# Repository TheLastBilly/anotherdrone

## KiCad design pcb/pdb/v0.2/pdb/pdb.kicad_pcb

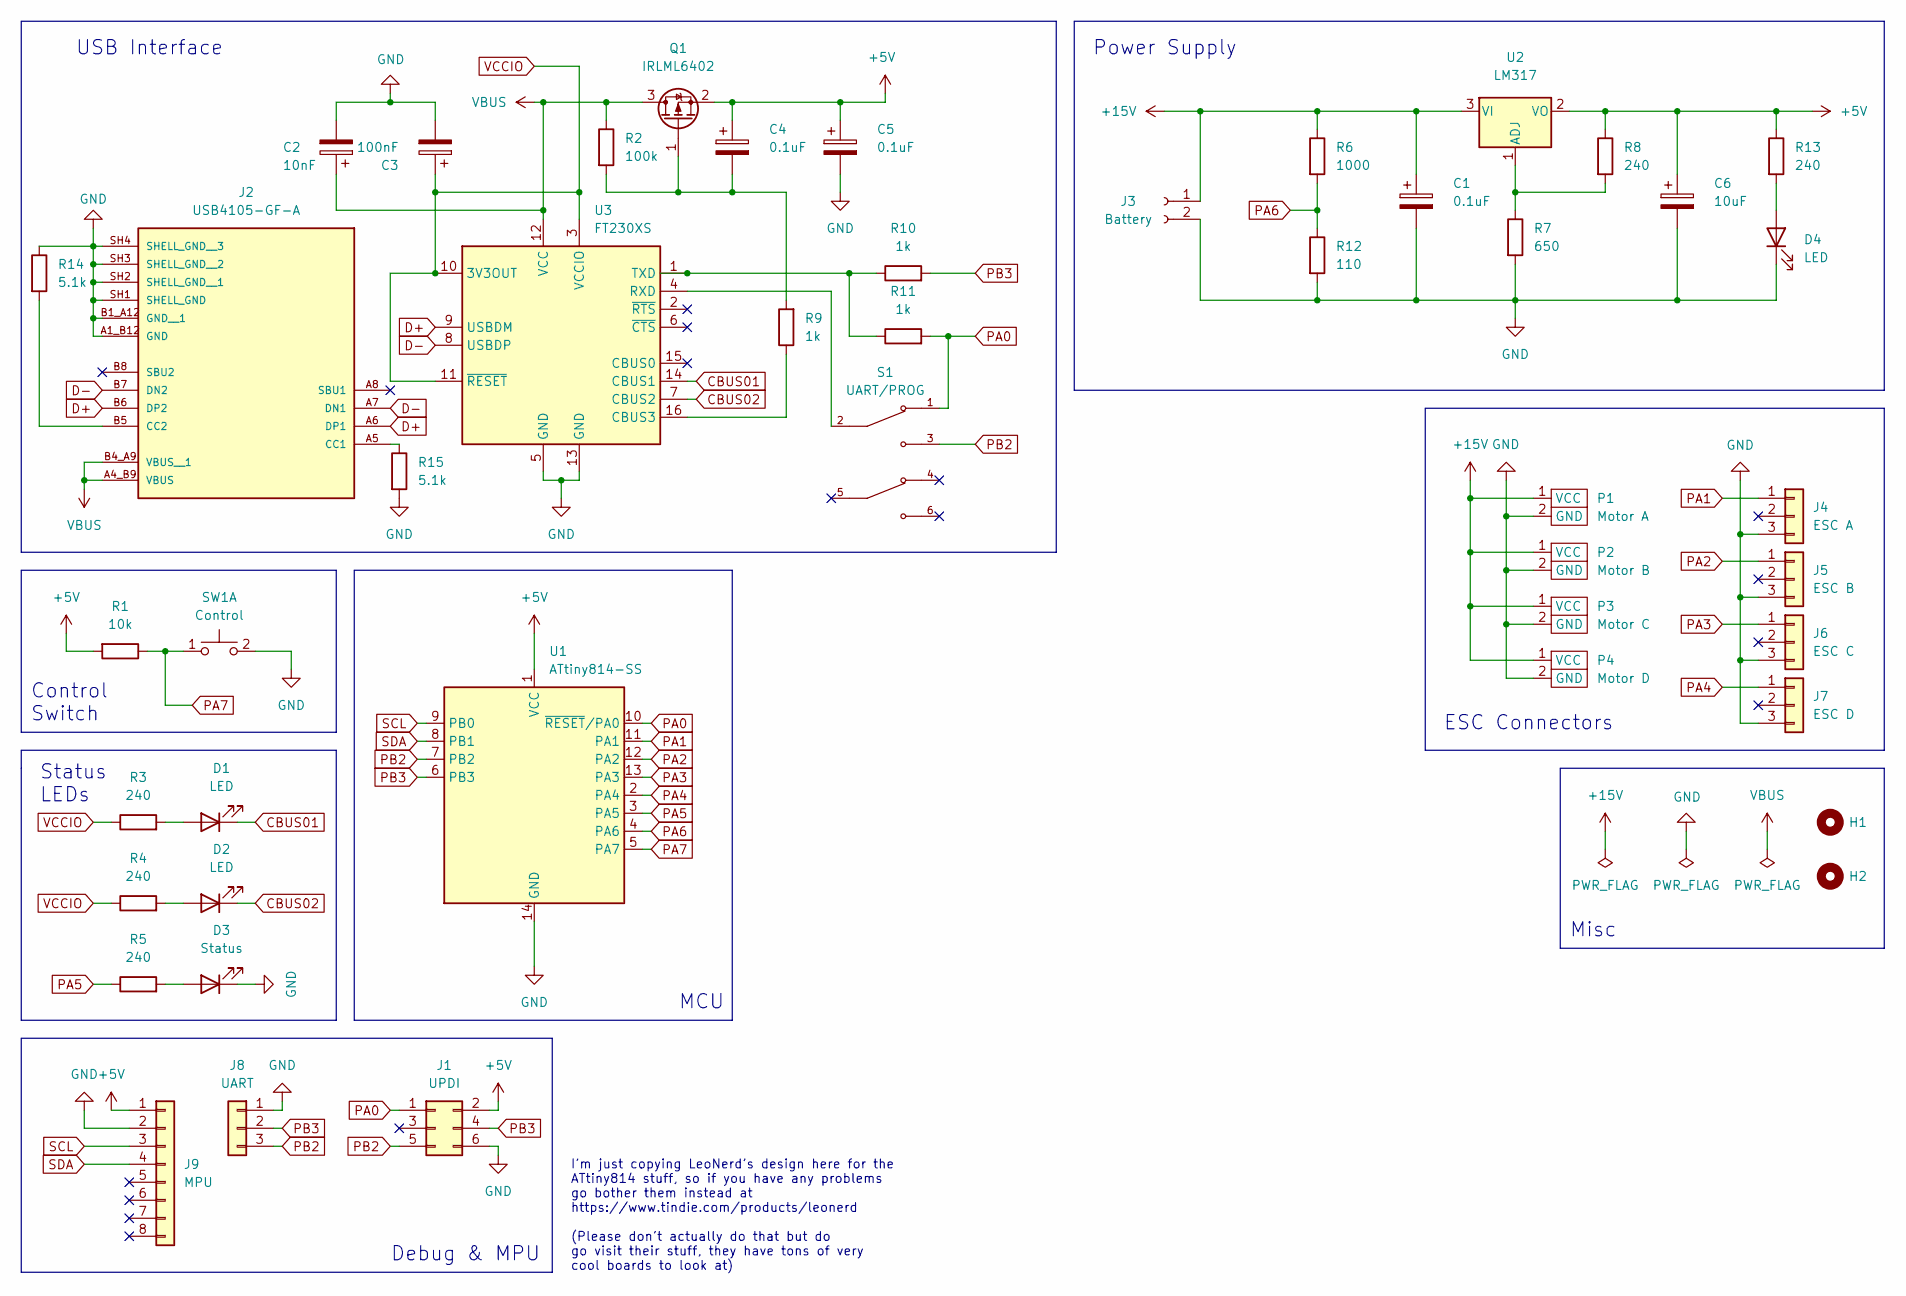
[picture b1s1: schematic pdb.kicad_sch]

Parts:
C1, C4, C5: 0.1uF; C_1206_3216Metric
C2: 10nF; C_1206_3216Metric
C3: 100nF; C_1206_3216Metric
C6: 10uF; C_1206_3216Metric
D1, D2, D4: LED; LED_0805_2012Metric
D3: Status; LED_0805_2012Metric
H1, H2: MountingHole; MountingHole_4.3mm_M4_Pad
J1: UPDI; PinSocket_2x03_P2.54mm_Vertical
J2: USB4105-GF-A; GCT_USB4105-GF-A; PARTREV B4
J3: Battery; ESC_Power_01x02
J4: ESC A; PinSocket_1x03_P2.54mm_Vertical
J5: ESC B; PinSocket_1x03_P2.54mm_Vertical
J6: ESC C; PinSocket_1x03_P2.54mm_Vertical
J7: ESC D; PinSocket_1x03_P2.54mm_Vertical
J8: UART; PinSocket_1x03_P2.54mm_Vertical
J9: MPU; PinSocket_1x08_P2.54mm_Vertical
P1: Motor A; ESC_Power_01x02
P2: Motor B; ESC_Power_01x02
P3: Motor C; ESC_Power_01x02
P4: Motor D; ESC_Power_01x02
Q1: IRLML6402; SOT-23
R1: 10k; R_1206_3216Metric
R2: 100k; R_1206_3216Metric
R3, R4, R5, R8, R13: 240; R_1206_3216Metric
R6: 1000; R_1206_3216Metric
R7: 650; R_1206_3216Metric
R9, R10, R11: 1k; R_1206_3216Metric
R12: 110; R_1206_3216Metric
R14, R15: 5.1k; R_1206_3216Metric
S1: UART/PROG; SW_CuK_JS202011AQN_DPDT_Angled; PARTREV 1.01
SW1: Control; SW_PUSH_6mm
U1: ATtiny814-SS; SOIC-14_3.9x8.7mm_P1.27mm
U2: LM317; SOT-223-3_TabPin2
U3: FT230XS; SSOP16-0.635-5X4MM

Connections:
+5V: C4.1, C5.1, C6.1, J1.2, J9.1, Q1.2 (S), R1.2, R8.1, R13.1, U1.1 (VCC), U2.2 (VO)
+15V: C1.1, J3.1, P1.1 (VCC), P2.1 (VCC), P3.1 (VCC), P4.1 (VCC), R6.1, U2.3 (VI)
CBUS01: D1.1 (K), U3.14 (CBUS1)
CBUS02: D2.1 (K), U3.7 (CBUS2)
D+: J2.A6 (DP1), J2.B6 (DP2), U3.9 (USBDM)
D-: J2.A7 (DN1), J2.B7 (DN2), U3.8 (USBDP)
GND: C1.2, C2.2, C3.2, C5.2, C6.2, D3.1 (K), D4.1 (K), J1.6, J2.A1_B12 (GND), J2.B1_A12 (GND__1), J2.SH1 (SHELL_GND), J2.SH2 (SHELL_GND__1), J2.SH3 (SHELL_GND__2), J2.SH4 (SHELL_GND__3), J3.2, J4.3, J5.3, J6.3, J7.3, J8.1, J9.2, P1.2 (GND), P2.2 (GND), P3.2 (GND), P4.2 (GND), R7.2, R12.2, R14.1, R15.2, SW1.2 (D), U1.14 (GND), U3.5 (GND), U3.13 (GND)
unnamed: C4.2, Q1.1 (G), R2.2, R9.2
unnamed: D1.2 (A), R3.2
unnamed: D2.2 (A), R4.2
unnamed: D3.2 (A), R5.2
unnamed: D4.2 (A), R13.2
unnamed: J2.A5 (CC1), R15.1
unnamed: J2.B5 (CC2), R14.2
unnamed: R7.1, R8.2, U2.1 (ADJ)
unnamed: R9.1, U3.16 (CBUS3)
unnamed: R10.1, R11.1, U3.1 (TXD)
unnamed: S1.2, U3.4 (RXD)
PA0: J1.1, R11.2, S1.1, U1.10 (~RESET/PA0)
PA1: J4.1, U1.11 (PA1)
PA2: J5.1, U1.12 (PA2)
PA3: J6.1, U1.13 (PA3)
PA4: J7.1, U1.2 (PA4)
PA5: R5.1, U1.3 (PA5)
PA6: R6.2, R12.1, U1.4 (PA6)
PA7: R1.1, SW1.1 (C), U1.5 (PA7)
PB2: J1.5, J8.3, S1.3, U1.7 (PB2)
PB3: J1.4, J8.2, R10.2, U1.6 (PB3)
SCL: J9.3, U1.9 (PB0)
SDA: J9.4, U1.8 (PB1)
VBUS: C2.1, J2.A4_B9 (VBUS), J2.B4_A9 (VBUS__1), Q1.3 (D), R2.1, U3.12 (VCC)
VCCIO: C3.1, R3.1, R4.1, U3.3 (VCCIO), U3.10 (3V3OUT), U3.11 (~RESET)

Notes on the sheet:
ESC Connectors
USB Interface
MCU
Control Switch
I'm just copying LeoNerd's design here for the ATtiny814 stuff, so if you have any problems go bother them instead at https://www.tindie.com/products/leonerd (Please don't actually do that but do go visit their stuff, they have tons of very cool boards to look at)
Misc
Debug & MPU
Power Supply
Status LEDs

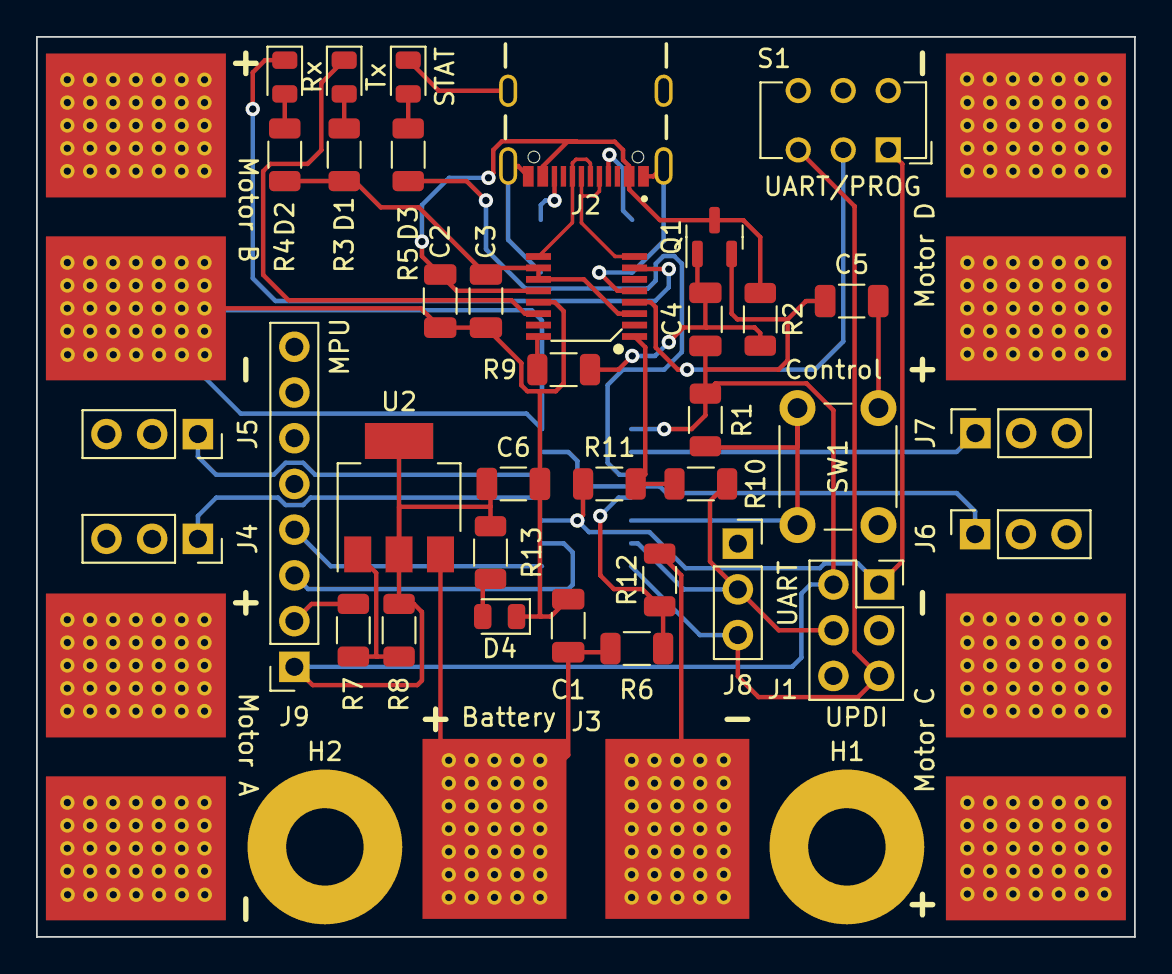
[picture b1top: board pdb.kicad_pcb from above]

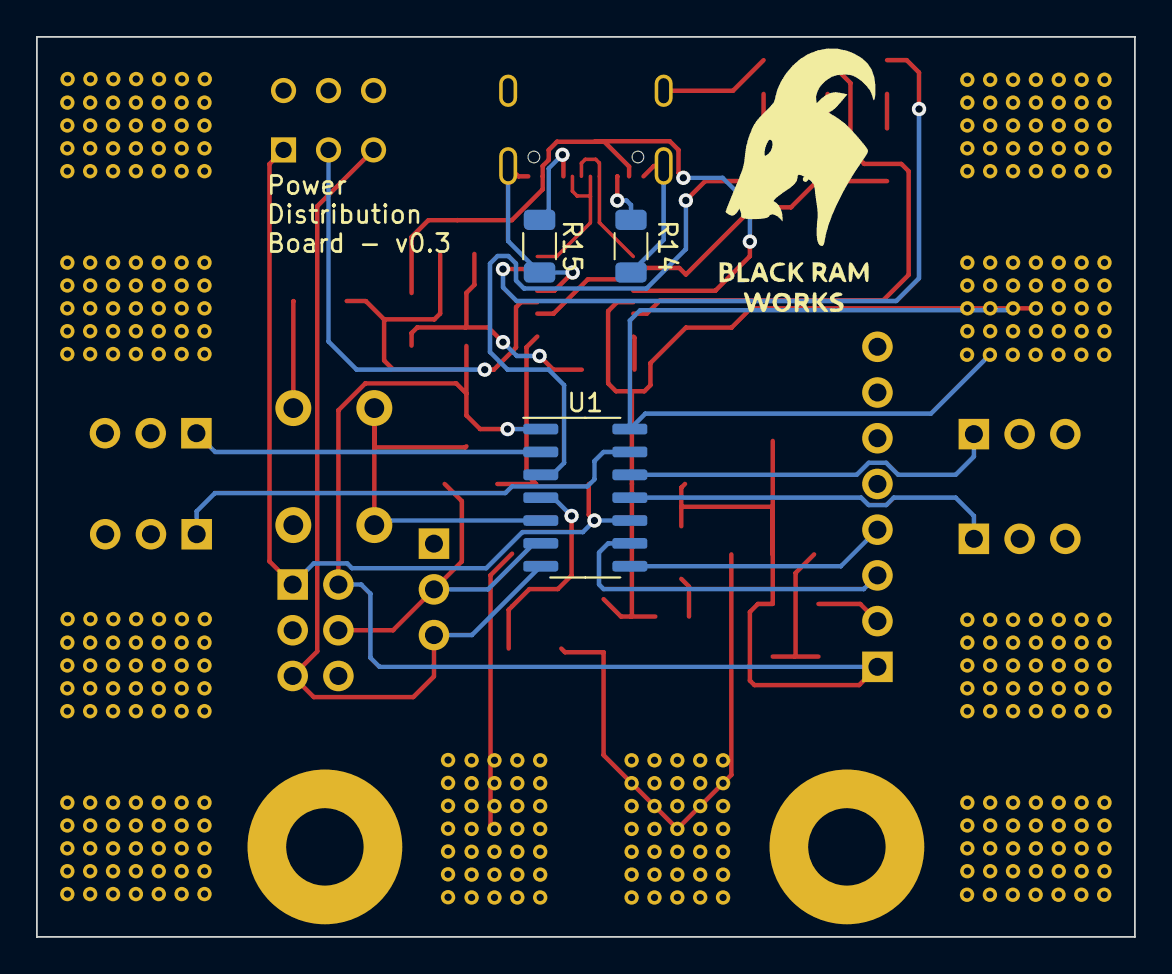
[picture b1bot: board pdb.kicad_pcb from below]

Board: 4 copper layers, 61.0 x 50.0 mm, 46 parts (3 on the bottom side), 32 nets.

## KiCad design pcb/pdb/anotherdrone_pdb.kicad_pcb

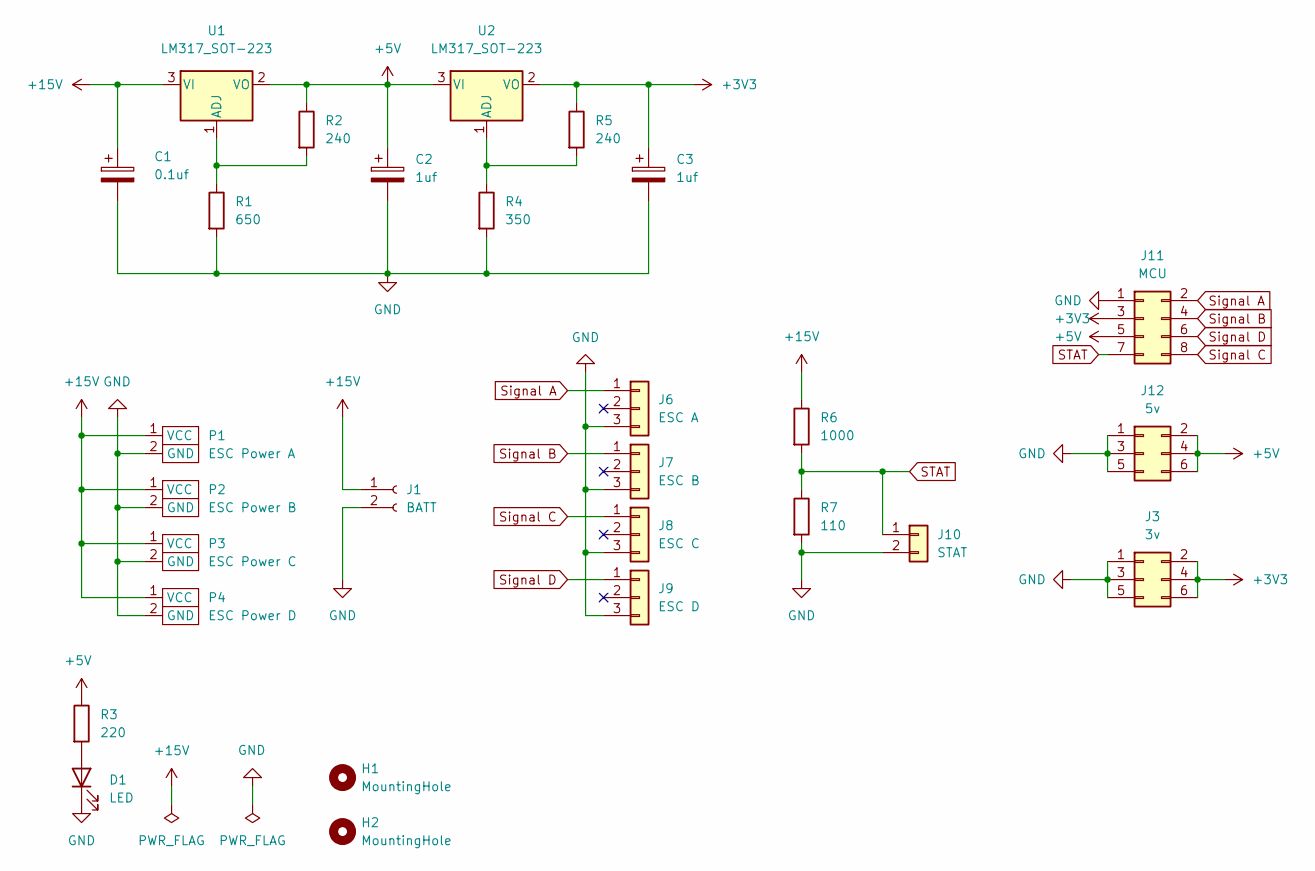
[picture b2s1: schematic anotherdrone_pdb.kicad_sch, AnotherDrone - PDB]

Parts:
C1: 0.1uf; C_1206_3216Metric
C2, C3: 1uf; C_1206_3216Metric
D1: LED; LED_0805_2012Metric
H1, H2: MountingHole; MountingHole_4.3mm_M4_Pad
J1: BATT; ESC_Power_01x02
J3: 3v; PinSocket_2x03_P2.54mm_Vertical
J6: ESC A; PinSocket_1x03_P2.54mm_Vertical
J7: ESC B; PinSocket_1x03_P2.54mm_Vertical
J8: ESC C; PinSocket_1x03_P2.54mm_Vertical
J9: ESC D; PinSocket_1x03_P2.54mm_Vertical
J10: STAT; PinSocket_1x02_P2.54mm_Vertical
J11: MCU; PinSocket_2x04_P2.54mm_Vertical
J12: 5v; PinSocket_2x03_P2.54mm_Vertical
P1: ESC Power A; ESC_Power_01x02
P2: ESC Power B; ESC_Power_01x02
P3: ESC Power C; ESC_Power_01x02
P4: ESC Power D; ESC_Power_01x02
R1: 650; R_1206_3216Metric
R2, R5: 240; R_1206_3216Metric
R3: 220; R_1206_3216Metric
R4: 350; R_1206_3216Metric
R6: 1000; R_1206_3216Metric
R7: 110; R_1206_3216Metric
U1, U2: LM317_SOT-223; SOT-223-3_TabPin2

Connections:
+3V3: C3.1, J3.2, J3.4, J3.6, J11.3, R5.1, U2.2 (VO)
+5V: C2.1, J11.5, J12.2, J12.4, J12.6, R2.1, R3.1, U1.2 (VO), U2.3 (VI)
+15V: C1.1, J1.1, P1.1 (VCC), P2.1 (VCC), P3.1 (VCC), P4.1 (VCC), R6.1, U1.3 (VI)
GND: C1.2, C2.2, C3.2, D1.1 (K), J1.2, J3.1, J3.3, J3.5, J6.3, J7.3, J8.3, J9.3, J10.2, J11.1, J12.1, J12.3, J12.5, P1.2 (GND), P2.2 (GND), P3.2 (GND), P4.2 (GND), R1.2, R4.2, R7.2
unnamed: D1.2 (A), R3.2
unnamed: R1.1, R2.2, U1.1 (ADJ)
unnamed: R4.1, R5.2, U2.1 (ADJ)
STAT: J10.1, J11.7, R6.2, R7.1
Signal A: J6.1, J11.2
Signal B: J7.1, J11.4
Signal C: J8.1, J11.8
Signal D: J9.1, J11.6

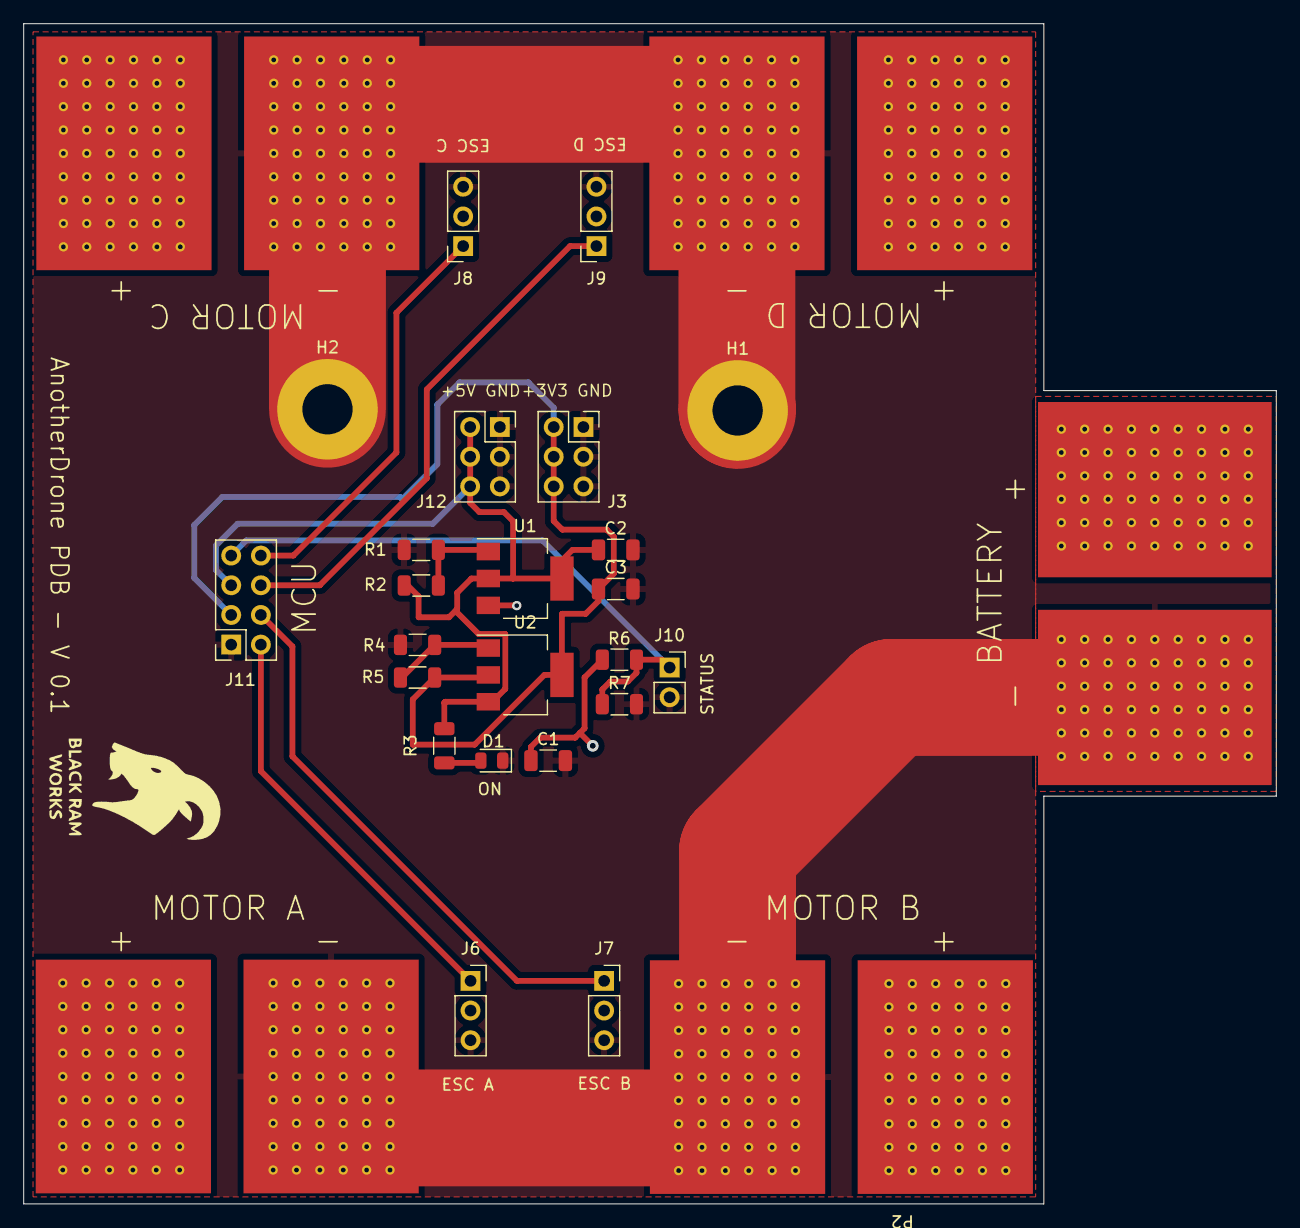
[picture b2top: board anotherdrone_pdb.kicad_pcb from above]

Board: 2 copper layers, 107.2 x 101.0 mm, 28 parts (0 on the bottom side), 12 nets.

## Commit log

2024-03-18 added taken link on .gitignore
2024-03-18 now using 15v and ground planes
2024-03-19 added logo
2024-03-23 updated gitignores
2024-03-23 added presentation files
2024-06-12 added platformio project
2024-06-12 moved controllers and oritentation functions into structs
2024-06-22 added frame freecad file
2024-06-23 added controller base and finished v2 arm. Started remote code
2024-06-24 communitcations working-ish
2024-06-25 adde dreport back on remote, added custom esc controller
2024-06-25 updated gitignore
2025-05-26 add source
2025-05-28 working version
2025-06-12 firmware: pdb: start attiny814 firmware
2025-06-19 pcb: add pdb v0.2 and v0.3
2025-06-19 firmware: moved to attiny814 firmware
2025-06-24 pcd: pdb: add USB port
2025-06-26 pcb: pdb: v0.2: fix traces
